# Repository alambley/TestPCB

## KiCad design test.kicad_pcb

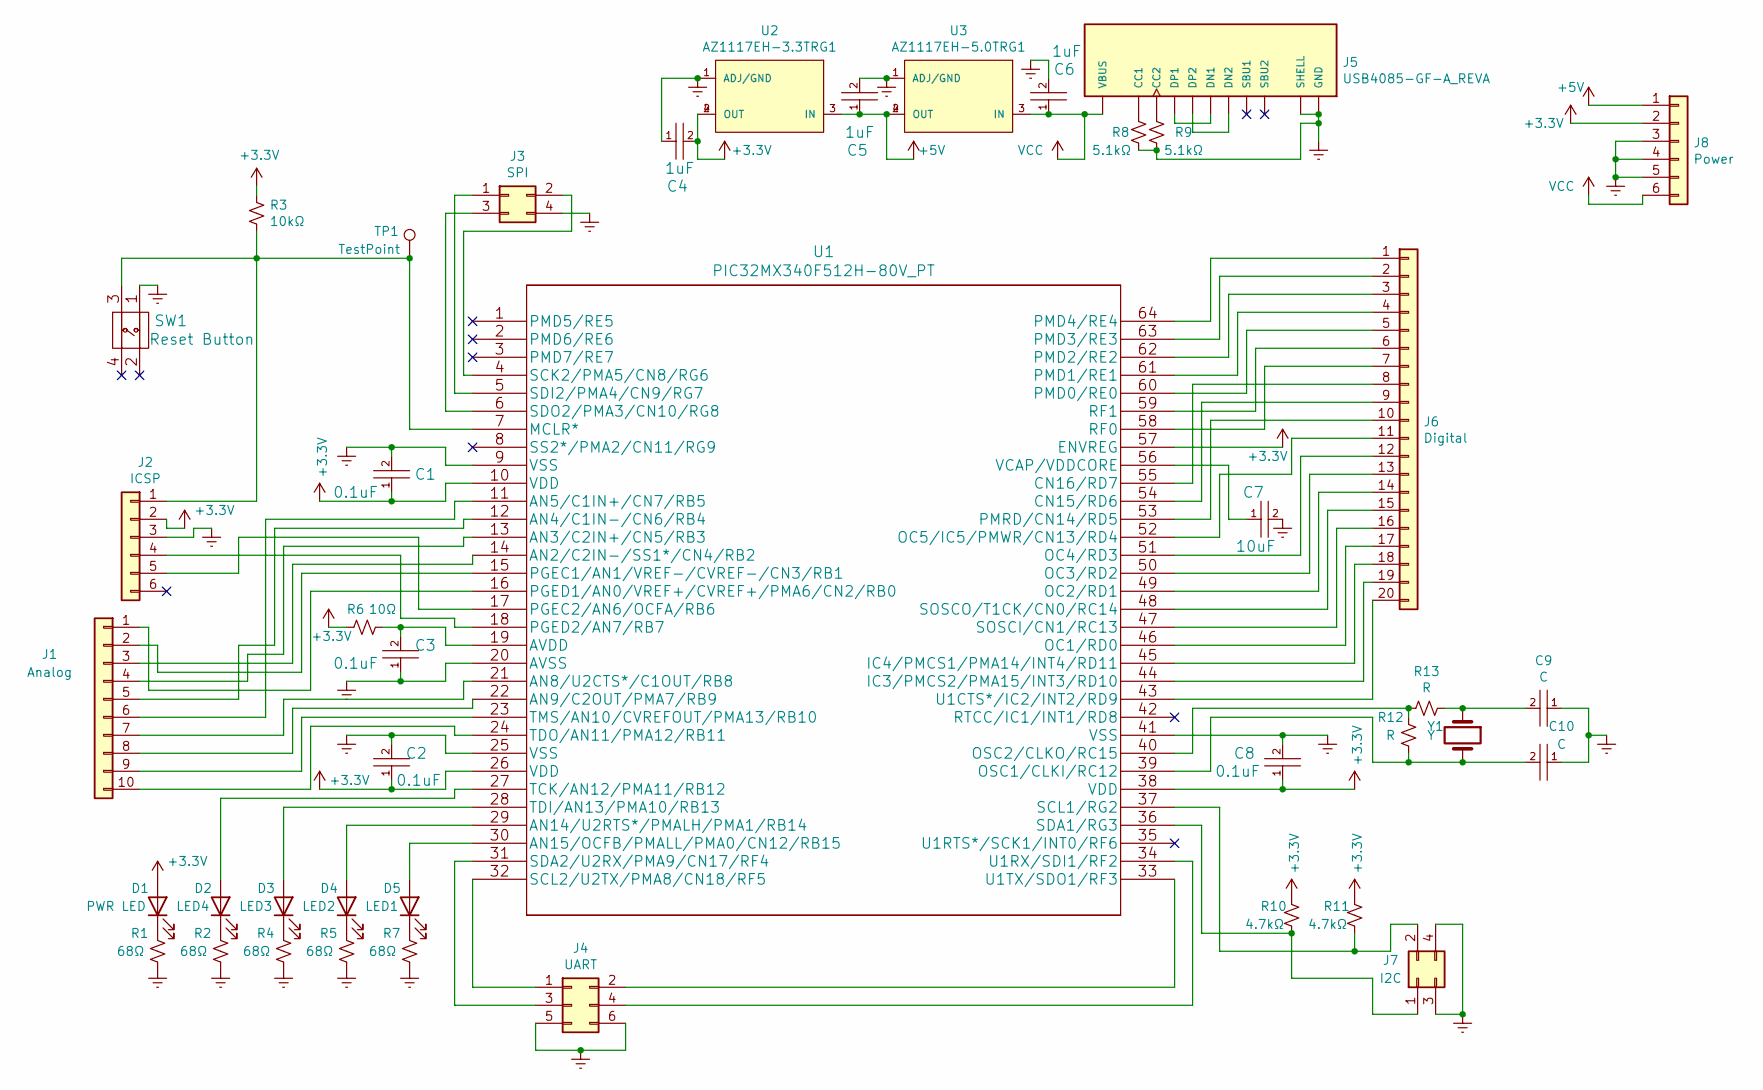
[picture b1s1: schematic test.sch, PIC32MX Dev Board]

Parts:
C1, C2, C3, C8: 0.1uF; 0603; Mfr # CL10B104KA8NNNC
C4, C5, C6: 1uF; 0603; Mfr # CL10A105KO8NNNC
C7: 10uF; 0603; Mfr # CL10A106MQ8NNNC
C9, C10: C; 0603
D1: PWR LED; 0603; Mfr # LTST-C191KGKT
D2: LED4; 0603; Mfr # LTST-C191KGKT
D3: LED3; 0603; Mfr # LTST-C191KGKT
D4: LED2; 0603; Mfr # LTST-C191KGKT
D5: LED1; 0603; Mfr # LTST-C191KGKT
J1: Analog; 02x05; Mfr # SSW-105-01-T-D
J2: ICSP; 01x06; Mfr # SSW-106-01-T-S
J3: SPI; 02x02; Mfr # SSW-102-01-T-D
J4: UART; 02x03; Mfr # SSW-103-01-T-D
J5: USB4085-GF-A_REVA; GCT_USB4085-GF-A_REVA; Mfr # USB4085-GF-A
J6: Digital; 02x20; Mfr # SSW-110-01-T-D
J7: I2C; 02x02; Mfr # SSW-102-01-T-D
J8: Power; 01x06; Mfr # SSW-106-01-T-S
R1, R2, R4, R5, R7: 68Ω; 0603; Mfr # RMCF0603FT68R0
R3: 10kΩ; 0603; Mfr # RMCF0603FT10K0
R6: 10Ω; 0603; Mfr # RMCF0603FT10R0
R8, R9: 5.1kΩ; 0603; Mfr # RC0603FR-075K1L
R10, R11: 4.7kΩ; 0603; Mfr # RMCF0603FT4K70
R12, R13: R; 0603
SW1: Reset Button; PTS647SK38SMTR2LFS; Mfr # PTS647SK38SMTR2LFS
TP1: TestPoint; TestPoint_Pad_D1.0mm
U1: PIC32MX340F512H-80V_PT; PIC32MX340F512H-80V&slash_PT
U2: AZ1117EH-3.3TRG1; SOT230P700X180-4N; Mfr # AZ1117EH-3.3TRG1
U3: AZ1117EH-5.0TRG1; SOT230P700X180-4N; Mfr # AZ1117EH-5.0TRG1
Y1: Y; 9B-8.000MAAJ-B

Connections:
+3V3: C1.1, C2.1, C4.2, C8.1, D1.2 (A), J2.2, J8.2, R3.1, R6.1, R10.2, R11.2, U1.10 (VDD), U1.26 (VDD), U1.38 (VDD), U1.57 (ENVREG), U2.2 (OUT), U2.4 (OUT)
+5V: C5.1, J8.1, U2.3 (IN), U3.2 (OUT), U3.4 (OUT)
GNDREF: C1.2, C2.2, C3.1, C4.1, C5.2, C6.2, C7.2, C8.2, C9.1, C10.1, J2.3, J3.4, J4.5, J4.6, J5.A1 (GND), J5.A12 (GND), J5.B1 (GND), J5.B12 (GND), J5.P1 (SHELL), J5.P2 (SHELL), J5.P3 (SHELL), J5.P4 (SHELL), J7.3, J7.4, J8.3, J8.4, J8.5, R1.1, R2.1, R4.1, R5.1, R7.1, R8.1, R9.1, SW1.1, U1.9 (VSS), U1.20 (AVSS), U1.25 (VSS), U1.41 (VSS), U2.1 (ADJ/GND), U3.1 (ADJ/GND)
unnamed: C3.2, R6.2, U1.19 (AVDD)
unnamed: C7.1, U1.56 (VCAP/VDDCORE)
unnamed: C9.2, R13.1, Y1.1
unnamed: C10.2, R12.2, U1.39 (OSC1/CLKI/RC12), Y1.2
unnamed: D1.1 (K), R1.2
unnamed: D2.1 (K), R2.2
unnamed: D2.2 (A), U1.27 (TCK/AN12/PMA11/RB12)
unnamed: D3.1 (K), R4.2
unnamed: D3.2 (A), U1.28 (TDI/AN13/PMA10/RB13)
unnamed: D4.1 (K), R5.2
unnamed: D4.2 (A), U1.29 (AN14/U2RTS*/PMALH/PMA1/RB14)
unnamed: D5.1 (K), R7.2
unnamed: D5.2 (A), U1.30 (AN15/OCFB/PMALL/PMA0/CN12/RB15)
unnamed: J1.1, U1.16 (PGED1/AN0/VREF+/CVREF+/PMA6/CN2/RB0)
unnamed: J1.2, U1.15 (PGEC1/AN1/VREF-/CVREF-/CN3/RB1)
unnamed: J1.3, U1.14 (AN2/C2IN-/SS1*/CN4/RB2)
unnamed: J1.4, U1.13 (AN3/C2IN+/CN5/RB3)
unnamed: J1.5, U1.12 (AN4/C1IN-/CN6/RB4)
unnamed: J1.6, U1.11 (AN5/C1IN+/CN7/RB5)
unnamed: J1.7, U1.21 (AN8/U2CTS*/C1OUT/RB8)
unnamed: J1.8, U1.22 (AN9/C2OUT/PMA7/RB9)
unnamed: J1.9, U1.23 (TMS/AN10/CVREFOUT/PMA13/RB10)
unnamed: J1.10, U1.24 (TDO/AN11/PMA12/RB11)
unnamed: J2.1, R3.2, SW1.3, TP1.1, U1.7 (MCLR*)
unnamed: J2.4, U1.18 (PGED2/AN7/RB7)
unnamed: J2.5, U1.17 (PGEC2/AN6/OCFA/RB6)
unnamed: J3.1, U1.5 (SDI2/PMA4/CN9/RG7)
unnamed: J3.2, U1.4 (SCK2/PMA5/CN8/RG6)
unnamed: J3.3, U1.6 (SDO2/PMA3/CN10/RG8)
unnamed: J4.1, U1.32 (SCL2/U2TX/PMA8/CN18/RF5)
unnamed: J4.2, U1.33 (U1TX/SDO1/RF3)
unnamed: J4.3, U1.31 (SDA2/U2RX/PMA9/CN17/RF4)
unnamed: J4.4, U1.34 (U1RX/SDI1/RF2)
unnamed: J5.A5 (CC1), R8.2
unnamed: J5.A6 (DP1), J5.A7 (DN1)
unnamed: J5.B5 (CC2), R9.2
unnamed: J5.B6 (DP2), J5.B7 (DN2)
unnamed: J6.1, U1.64 (PMD4/RE4)
unnamed: J6.2, U1.63 (PMD3/RE3)
unnamed: J6.3, U1.62 (PMD2/RE2)
unnamed: J6.4, U1.61 (PMD1/RE1)
unnamed: J6.5, U1.60 (PMD0/RE0)
unnamed: J6.6, U1.59 (RF1)
unnamed: J6.7, U1.58 (RF0)
unnamed: J6.8, U1.55 (CN16/RD7)
unnamed: J6.9, U1.54 (CN15/RD6)
unnamed: J6.10, U1.53 (PMRD/CN14/RD5)
unnamed: J6.11, U1.52 (OC5/IC5/PMWR/CN13/RD4)
unnamed: J6.12, U1.51 (OC4/RD3)
unnamed: J6.13, U1.50 (OC3/RD2)
unnamed: J6.14, U1.49 (OC2/RD1)
unnamed: J6.15, U1.48 (SOSCO/T1CK/CN0/RC14)
unnamed: J6.16, U1.47 (SOSCI/CN1/RC13)
unnamed: J6.17, U1.46 (OC1/RD0)
unnamed: J6.18, U1.45 (IC4/PMCS1/PMA14/INT4/RD11)
unnamed: J6.19, U1.44 (IC3/PMCS2/PMA15/INT3/RD10)
unnamed: J6.20, U1.43 (U1CTS*/IC2/INT2/RD9)
unnamed: J7.1, R10.1, U1.36 (SDA1/RG3)
unnamed: J7.2, R11.1, U1.37 (SCL1/RG2)
unnamed: R12.1, R13.2, U1.40 (OSC2/CLKO/RC15)
VCC: C6.1, J5.A4 (VBUS), J5.A9 (VBUS), J5.B4 (VBUS), J5.B9 (VBUS), J8.6, U3.3 (IN)

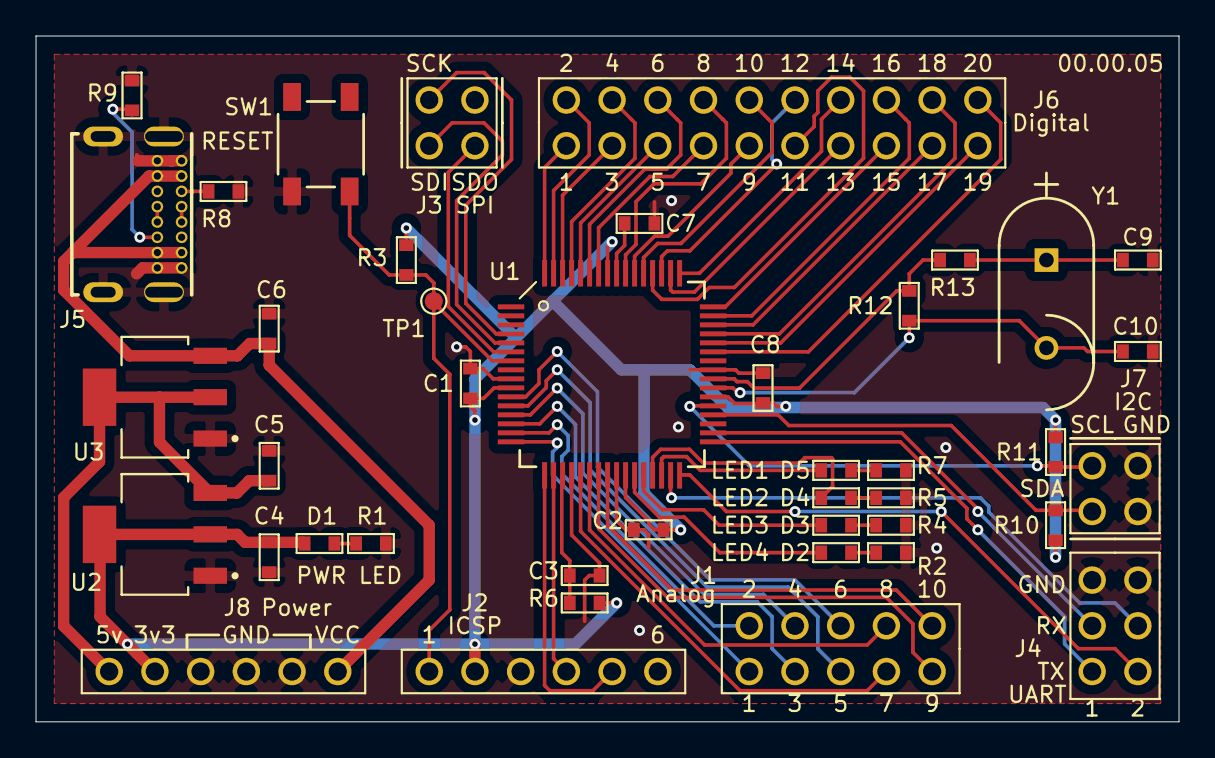
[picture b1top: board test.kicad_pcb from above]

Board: 2 copper layers, 63.5 x 38.1 mm, 42 parts (0 on the bottom side), 64 nets.

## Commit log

2020-11-01 init commit
2020-11-02 - Reworked schematic with more recognizable symbols, more information, more adherent to FAQ, etc. - Shifted from 4 layer to 2 layer - Removed all micro/hidden vias - Standardized footprints for all r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
2020-11-03 - Changed board size to 1" by 2" - added 40mil exclusion zone from board edges - changed default trace to 8 mil - changed exclusion to 8 mil - changed power traces to 12 mil - added more descriptive 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
2020-11-04 - Added 4 User LEDs - Added 1 Power LED - Added 5 68ohm resistors to complement above LEDs - Reshaped board to 1.8"-1.1" - Added pin 52 to / Removed pin 42 from GPIO header (traded an INT for an extr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
2020-11-05 - Changed PIC from MR to PT package for ease of soldering - Increased size from 2"-1.2"
2020-11-05 Made a few changes for boardhouse - Moved title silkscreen up like 10mil - Shifted mount holes from vias to an actual footprint
2020-11-24 - Began work on dev board V2
2020-11-25 Finished following changes... - Removed SMD test points for power and replaced with USB-C port - Added 2 voltage regulators for 5v and 3v3 - Added a 6 port power header for 5v, 3v3, GND, and VIN - Ad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
2020-12-05 - added pic32 mfr and mfr # because why not
2021-05-12 - Added some python scripts that helped me with various things
2021-05-13 - generated BOM csv now has components sorted by amount in schematic for ease of ordering - added Y character for grabbing crystals from schematic

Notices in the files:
parts and their libraries:
Copyright 2016 Accelerated Designs. All rights reserved.
